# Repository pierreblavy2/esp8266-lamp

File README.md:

# esp8266-lamp
A wifi controllable RGB light, based on esp8266.
The default access point ssid is <code>lamp</code>, the password is <code>magicword</code>, and the adress is <code>http://192.168.4.1</code>.
NOTE the curent version works only with http, not https.

# The project contains 
- the PCB design (kicad and gerber) CC-BY-SA 3.0
- the 3D printer files (3d) CC-BY-SA 3.0
- the arduino code (arduino) Some file MIT, some GPL-3.0, see details in Licenses.txt
- For details about licences, see Licenses.txt

# Images

# Thanks
Thank a lot to Syntax and Uru, who helped a lot for this project!

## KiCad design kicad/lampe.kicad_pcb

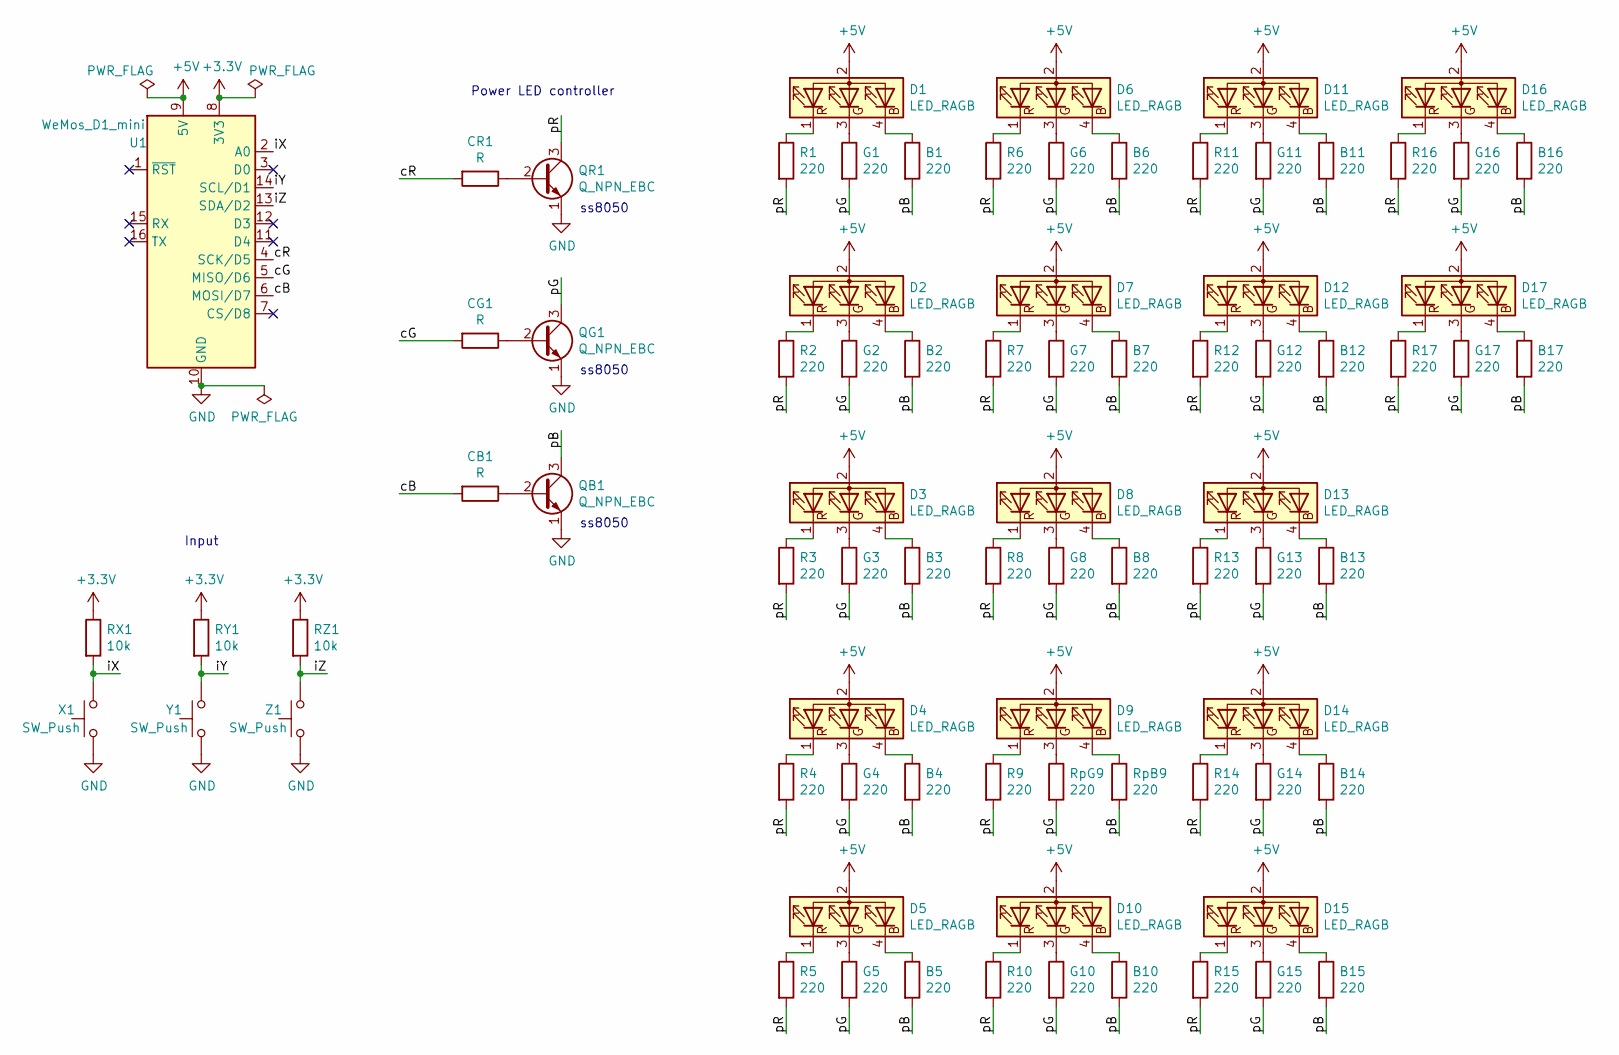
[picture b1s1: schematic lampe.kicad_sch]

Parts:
B1, B2, B3, B4, B5, B6, B7, B8, B10, B11, B12, B15, B16, B17: 220; R_Axial_DIN0207_L6.3mm_D2.5mm_P2.54mm_Vertical
B13, B14: 220; R_Axial_DIN0207_L6.3mm_D2.5mm_P10.16mm_Horizontal
CB1: R; R_Axial_DIN0207_L6.3mm_D2.5mm_P2.54mm_Vertical
CG1: R; R_Axial_DIN0207_L6.3mm_D2.5mm_P2.54mm_Vertical
CR1: R; R_Axial_DIN0207_L6.3mm_D2.5mm_P2.54mm_Vertical
D1, D2, D3, D4, D5, D6, D7, D8, D9, D10, D11, D12, D13, D14, D15, D16, D17: LED_RAGB; LED_RAGB_5mm_v2
G1, G2, G3, G4, G5, G6, G7, G8, G10, G11, G12, G15, G16, G17: 220; R_Axial_DIN0207_L6.3mm_D2.5mm_P2.54mm_Vertical
G13, G14: 220; R_Axial_DIN0207_L6.3mm_D2.5mm_P10.16mm_Horizontal
QB1: Q_NPN_EBC; Q_NPN_EBC_TO-92_v2
QG1: Q_NPN_EBC; Q_NPN_EBC_TO-92_v2
QR1: Q_NPN_EBC; Q_NPN_EBC_TO-92_v2
R1, R2, R3, R4, R5, R6, R7, R8, R9, R10, R11, R12, R13, R15, R16, R17: 220; R_Axial_DIN0207_L6.3mm_D2.5mm_P2.54mm_Vertical
R14: 220; R_Axial_DIN0207_L6.3mm_D2.5mm_P10.16mm_Horizontal
RX1: 10k; R_Axial_DIN0207_L6.3mm_D2.5mm_P2.54mm_Vertical
RY1: 10k; R_Axial_DIN0207_L6.3mm_D2.5mm_P2.54mm_Vertical
RZ1: 10k; R_Axial_DIN0207_L6.3mm_D2.5mm_P2.54mm_Vertical
RpB9: 220; R_Axial_DIN0207_L6.3mm_D2.5mm_P2.54mm_Vertical
RpG9: 220; R_Axial_DIN0207_L6.3mm_D2.5mm_P2.54mm_Vertical
U1: WeMos_D1_mini; WEMOS_D1_mini_light
X1: SW_Push; SW_PUSH_6mm
Y1: SW_Push; SW_PUSH_6mm
Z1: SW_Push; SW_PUSH_6mm

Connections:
+3V3: RX1.1, RY1.1, RZ1.1, U1.8 (3V3)
+5V: D1.2 (A), D2.2 (A), D3.2 (A), D4.2 (A), D5.2 (A), D6.2 (A), D7.2 (A), D8.2 (A), D9.2 (A), D10.2 (A), D11.2 (A), D12.2 (A), D13.2 (A), D14.2 (A), D15.2 (A), D16.2 (A), D17.2 (A), U1.9 (5V)
/cB: CB1.2, U1.6 (MOSI/D7)
/cG: CG1.2, U1.5 (MISO/D6)
/cR: CR1.2, U1.4 (SCK/D5)
/iX: RX1.2, U1.2 (A0), X1.2
/iY: RY1.2, U1.14 (SCL/D1), Y1.2
/iZ: RZ1.2, U1.13 (SDA/D2), Z1.2
/pB: B1.2, B2.2, B3.2, B4.2, B5.2, B6.2, B7.2, B8.2, B10.2, B11.2, B12.2, B13.2, B14.2, B15.2, B16.2, B17.2, QB1.3 (C), RpB9.2
/pG: G1.2, G2.2, G3.2, G4.2, G5.2, G6.2, G7.2, G8.2, G10.2, G11.2, G12.2, G13.2, G14.2, G15.2, G16.2, G17.2, QG1.3 (C), RpG9.2
/pR: QR1.3 (C), R1.2, R2.2, R3.2, R4.2, R5.2, R6.2, R7.2, R8.2, R9.2, R10.2, R11.2, R12.2, R13.2, R14.2, R15.2, R16.2, R17.2
GND: QB1.1 (E), QG1.1 (E), QR1.1 (E), U1.10 (GND), X1.1, Y1.1, Z1.1
unnamed: B1.1, D1.4 (BK)
unnamed: B2.1, D2.4 (BK)
unnamed: B3.1, D3.4 (BK)
unnamed: B4.1, D4.4 (BK)
unnamed: B5.1, D5.4 (BK)
unnamed: B6.1, D6.4 (BK)
unnamed: B7.1, D7.4 (BK)
unnamed: B8.1, D8.4 (BK)
unnamed: B10.1, D10.4 (BK)
unnamed: B11.1, D11.4 (BK)
unnamed: B12.1, D12.4 (BK)
unnamed: B13.1, D13.4 (BK)
unnamed: B14.1, D14.4 (BK)
unnamed: B15.1, D15.4 (BK)
unnamed: B16.1, D16.4 (BK)
unnamed: B17.1, D17.4 (BK)
unnamed: CB1.1, QB1.2 (B)
unnamed: CG1.1, QG1.2 (B)
unnamed: CR1.1, QR1.2 (B)
unnamed: D1.1 (RK), R1.1
unnamed: D1.3 (GK), G1.1
unnamed: D2.1 (RK), R2.1
unnamed: D2.3 (GK), G2.1
unnamed: D3.1 (RK), R3.1
unnamed: D3.3 (GK), G3.1
unnamed: D4.1 (RK), R4.1
unnamed: D4.3 (GK), G4.1
unnamed: D5.1 (RK), R5.1
unnamed: D5.3 (GK), G5.1
unnamed: D6.1 (RK), R6.1
unnamed: D6.3 (GK), G6.1
unnamed: D7.1 (RK), R7.1
unnamed: D7.3 (GK), G7.1
unnamed: D8.1 (RK), R8.1
unnamed: D8.3 (GK), G8.1
unnamed: D9.1 (RK), R9.1
unnamed: D9.3 (GK), RpG9.1
unnamed: D9.4 (BK), RpB9.1
unnamed: D10.1 (RK), R10.1
unnamed: D10.3 (GK), G10.1
unnamed: D11.1 (RK), R11.1
unnamed: D11.3 (GK), G11.1
unnamed: D12.1 (RK), R12.1
unnamed: D12.3 (GK), G12.1
unnamed: D13.1 (RK), R13.1
unnamed: D13.3 (GK), G13.1
unnamed: D14.1 (RK), R14.1
unnamed: D14.3 (GK), G14.1
unnamed: D15.1 (RK), R15.1
unnamed: D15.3 (GK), G15.1
unnamed: D16.1 (RK), R16.1
unnamed: D16.3 (GK), G16.1
unnamed: D17.1 (RK), R17.1
unnamed: D17.3 (GK), G17.1

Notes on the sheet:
Power LED controller
ss8050
Input

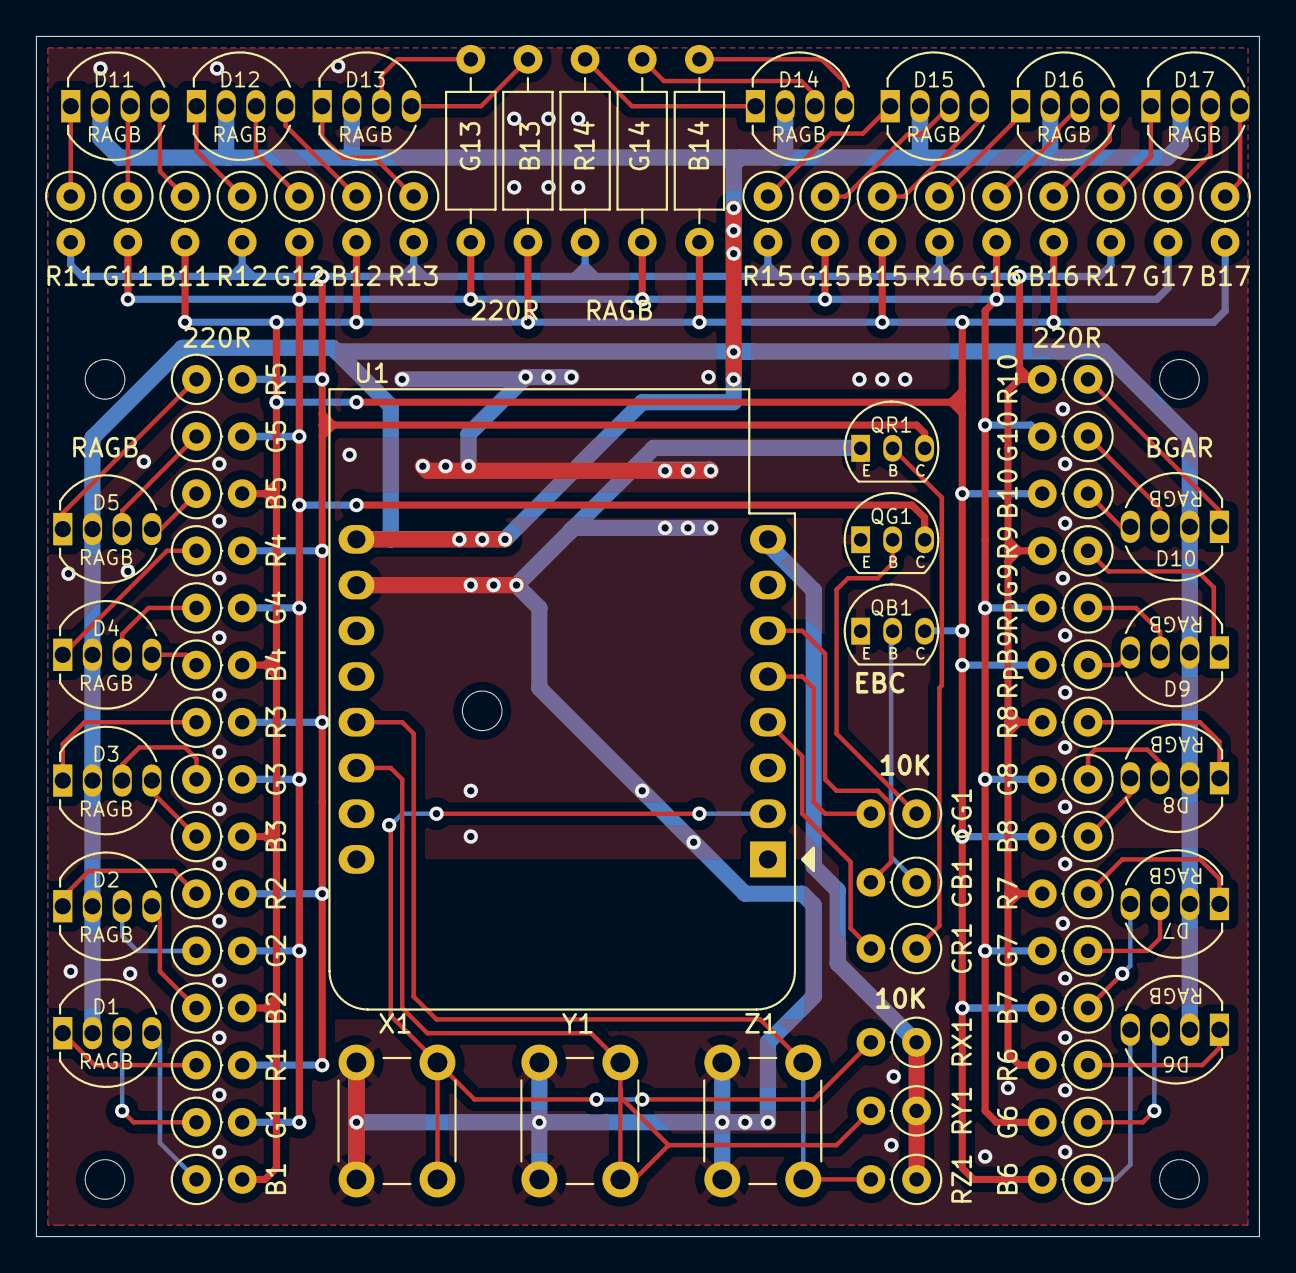
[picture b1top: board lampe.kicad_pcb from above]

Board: 2 copper layers, 67.9 x 66.7 mm, 81 parts (0 on the bottom side), 66 nets.

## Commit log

2022-03-28 Initial commit
    The lamp and the web site works
2022-03-31 Update Wifi.hpp
    BUGFIX : default my_ssid
2022-04-12 +transistor and led footprint edit => spread the legs... euh
